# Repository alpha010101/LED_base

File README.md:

チップLEDを筐体に実装するための補助基板

SchematicとPCB_LayoutをAutodesk-Eagle無償版で入力し、elecrowで製造することを前提にガーバーを作成

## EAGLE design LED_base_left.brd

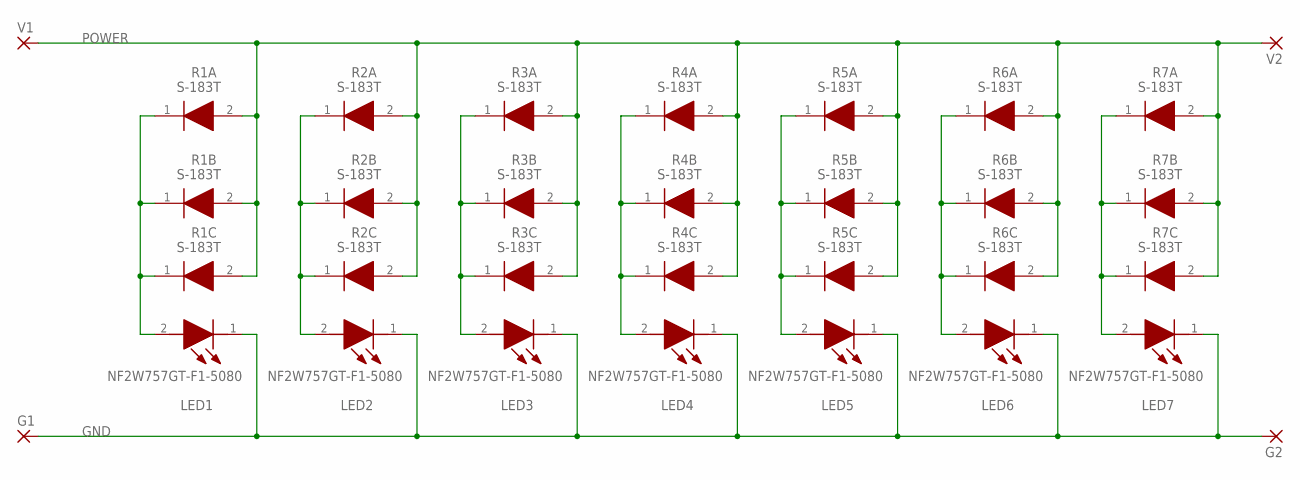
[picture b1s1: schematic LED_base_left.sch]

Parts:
G1: SMD_FULL; SMD3.5-2.5
G2: SMD_HALF; SMD1.75-2.5
LED1, LED2, LED3, LED4, LED5, LED6, LED7: NF2W757GT-F1-5080; NF2W757DRTX
R1A, R1B, R1C, R2A, R2B, R2C, R3A, R3B, R3C, R4A, R4B, R4C, R5A, R5B, R5C, R6A, R6B, R6C, R7A, R7B, R7C: S-183T; SODFL3516X70NX
V1: SMD_FULL; SMD3.5-2.5
V2: SMD_HALF; SMD1.75-2.5

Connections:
GND: G1.1, G2.1, LED1.1 (K), LED2.1 (K), LED3.1 (K), LED4.1 (K), LED5.1 (K), LED6.1 (K), LED7.1 (K)
unnamed: LED1.2 (A), R1A.1 (K), R1B.1 (K), R1C.1 (K)
unnamed: LED2.2 (A), R2A.1 (K), R2B.1 (K), R2C.1 (K)
unnamed: LED3.2 (A), R3A.1 (K), R3B.1 (K), R3C.1 (K)
unnamed: LED4.2 (A), R4A.1 (K), R4B.1 (K), R4C.1 (K)
unnamed: LED5.2 (A), R5A.1 (K), R5B.1 (K), R5C.1 (K)
unnamed: LED6.2 (A), R6A.1 (K), R6B.1 (K), R6C.1 (K)
unnamed: LED7.2 (A), R7A.1 (K), R7B.1 (K), R7C.1 (K)
POWER: R1A.2 (A), R1B.2 (A), R1C.2 (A), R2A.2 (A), R2B.2 (A), R2C.2 (A), R3A.2 (A), R3B.2 (A), R3C.2 (A), R4A.2 (A), R4B.2 (A), R4C.2 (A), R5A.2 (A), R5B.2 (A), R5C.2 (A), R6A.2 (A), R6B.2 (A), R6C.2 (A), R7A.2 (A), R7B.2 (A), R7C.2 (A), V1.1, V2.1

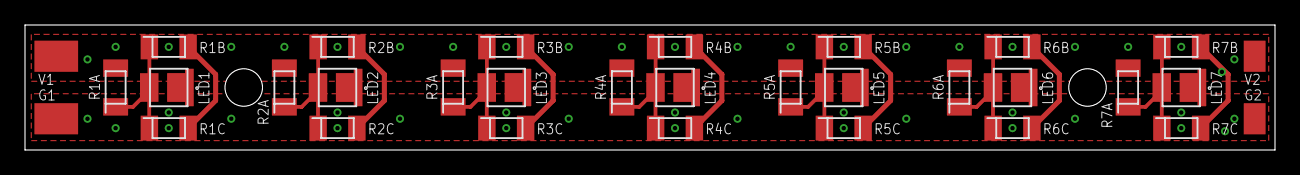
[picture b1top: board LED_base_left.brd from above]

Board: 2 copper layers, 100.0 x 10.0 mm, 32 parts (0 on the bottom side), 9 nets.

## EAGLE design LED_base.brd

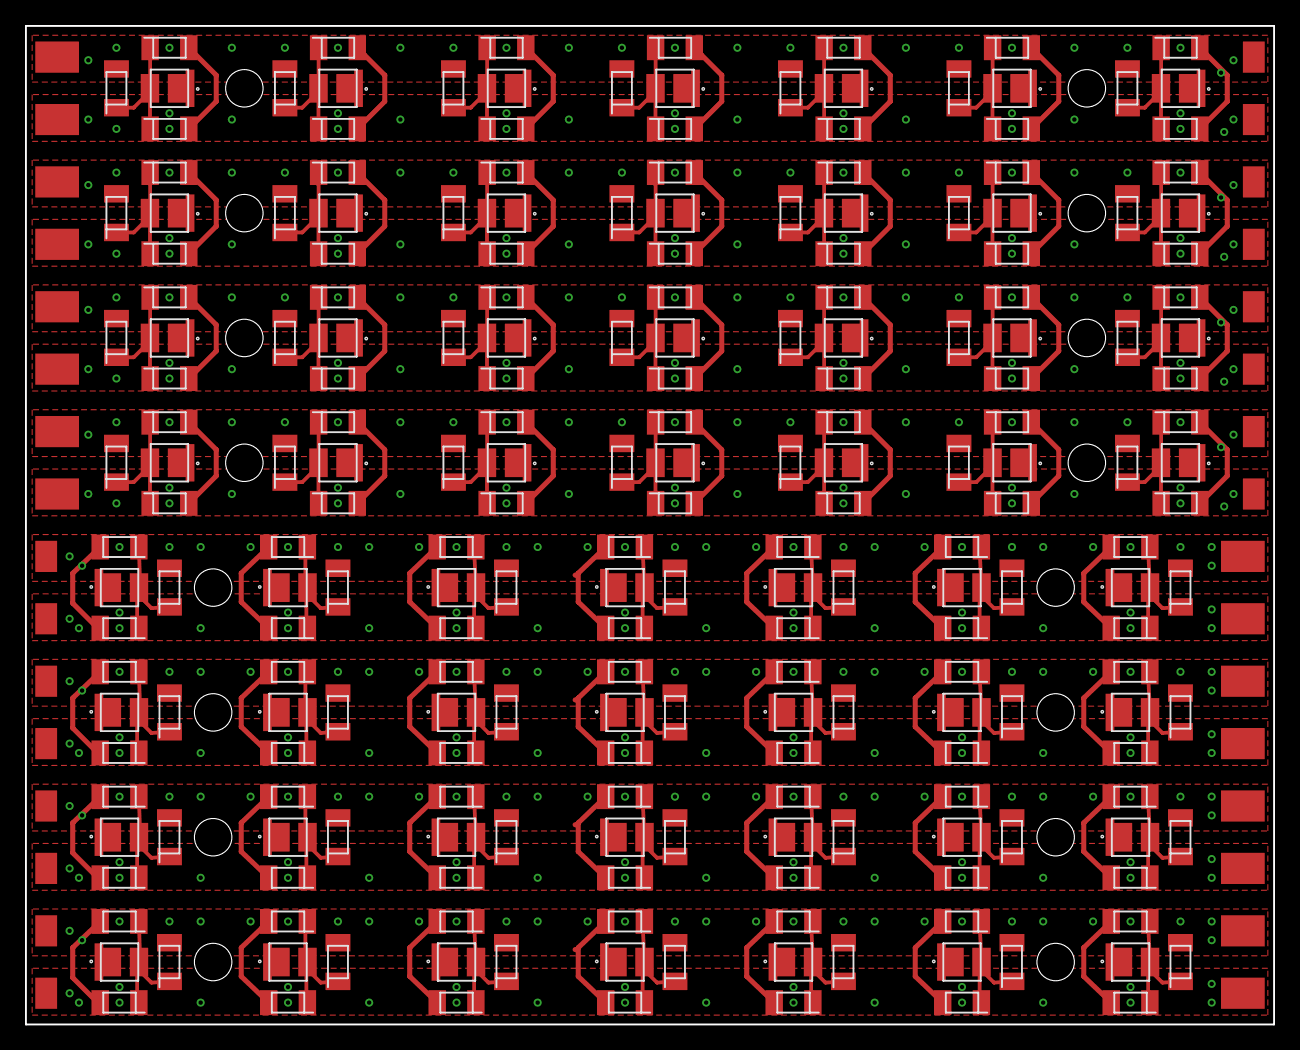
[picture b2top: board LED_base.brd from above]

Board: 2 copper layers, 100.0 x 80.0 mm, 256 parts (0 on the bottom side), 72 nets.

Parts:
G1, G4, G6, G8, G10, G12, G14, G16: SMD1.75-2.5
G2, G3, G5, G7, G9, G11, G13, G15: SMD3.5-2.5
LED1, LED2, LED3, LED4, LED5, LED6, LED7, LED8, LED9, LED10, LED11, LED12, LED13, LED14, LED15, LED16, LED17, LED18, LED19, LED20, LED21, LED22, LED23, LED24, LED25, LED26, LED27, LED28, LED29, LED30, LED31, LED32, LED33, LED34, LED35, LED36, LED37, LED38, LED39, LED40, LED41, LED42, LED43, LED44, LED45, LED46, LED47, LED48, LED49, LED50, LED51, LED52, LED53, LED54, LED55, LED56: NF2W757GT-F1-5080; NF2W757DRTX
R1A, R1A1, R1A2, R1A3, R1B, R1B1, R1B2, R1B3, R1C, R1C1, R1C2, R1C3, R2A, R2A1, R2A2, R2A3, R2B, R2B1, R2B2, R2B3, R2C, R2C1, R2C2, R2C3, R3A, R3A1, R3A2, R3A3, R3B, R3B1, R3B2, R3B3, R3C, R3C1, R3C2, R3C3, R4A, R4A1, R4A2, R4A3, R4B, R4B1, R4B2, R4B3, R4C, R4C1, R4C2, R4C3, R5A, R5A1, R5A2, R5A3, R5B, R5B1, R5B2, R5B3, R5C, R5C1, R5C2, R5C3, R6A, R6A1, R6A2, R6A3, R6B, R6B1, R6B2, R6B3, R6C, R6C1, R6C2, R6C3, R7A, R7A1, R7A2, R7A3, R7B, R7B1, R7B2, R7B3, R7C, R7C1, R7C2, R7C3, R8A, R8A1, R8A2, R8A3, R8B, R8B1, R8B2, R8B3, R8C, R8C1, R8C2, R8C3, R9A, R9A1, R9A2, R9A3, R9B, R9B1, R9B2, R9B3, R9C, R9C1, R9C2, R9C3, R10A, R10A1, R10A2, R10A3, R10B, R10B1, R10B2, R10B3, R10C, R10C1, R10C2, R10C3, R11A, R11A1, R11A2, R11A3, R11B, R11B1, R11B2, R11B3, R11C, R11C1, R11C2, R11C3, R12A, R12A1, R12A2, R12A3, R12B, R12B1, R12B2, R12B3, R12C, R12C1, R12C2, R12C3, R13A, R13A1, R13A2, R13A3, R13B, R13B1, R13B2, R13B3, R13C, R13C1, R13C2, R13C3, R14A, R14A1, R14A2, R14A3, R14B, R14B1, R14B2, R14B3, R14C, R14C1, R14C2, R14C3: S-183T; SODFL3516X70NX
V1, V3, V5, V7, V10, V12, V14, V16: SMD1.75-2.5
V2, V4, V6, V8, V9, V11, V13, V15: SMD3.5-2.5

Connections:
GND: G1.1, G2.1, LED8.1, LED9.1, LED10.1, LED11.1, LED12.1, LED13.1, LED14.1
GND1: G3.1, G4.1, LED1.1, LED2.1, LED3.1, LED4.1, LED5.1, LED6.1, LED7.1
GND2: G5.1, G6.1, LED15.1, LED16.1, LED17.1, LED18.1, LED19.1, LED20.1, LED21.1
GND3: G7.1, G8.1, LED22.1, LED23.1, LED24.1, LED25.1, LED26.1, LED27.1, LED28.1
GND4: G9.1, G10.1, LED29.1, LED30.1, LED31.1, LED32.1, LED33.1, LED34.1, LED35.1
GND5: G11.1, G12.1, LED36.1, LED37.1, LED38.1, LED39.1, LED40.1, LED41.1, LED42.1
GND6: G13.1, G14.1, LED43.1, LED44.1, LED45.1, LED46.1, LED47.1, LED48.1, LED49.1
GND7: G15.1, G16.1, LED50.1, LED51.1, LED52.1, LED53.1, LED54.1, LED55.1, LED56.1
unnamed: LED8.2, R8A.1, R8B.1, R8C.1
unnamed: LED9.2, R9A.1, R9B.1, R9C.1
unnamed: LED10.2, R10A.1, R10B.1, R10C.1
unnamed: LED11.2, R11A.1, R11B.1, R11C.1
unnamed: LED12.2, R12A.1, R12B.1, R12C.1
unnamed: LED13.2, R13A.1, R13B.1, R13C.1
unnamed: LED14.2, R14A.1, R14B.1, R14C.1
unnamed: LED6.2, R8A1.1, R8B1.1, R8C1.1
unnamed: LED7.2, R9A1.1, R9B1.1, R9C1.1
unnamed: LED1.2, R10A1.1, R10B1.1, R10C1.1
unnamed: LED2.2, R11A1.1, R11B1.1, R11C1.1
unnamed: LED3.2, R12A1.1, R12B1.1, R12C1.1
unnamed: LED4.2, R13A1.1, R13B1.1, R13C1.1
unnamed: LED5.2, R14A1.1, R14B1.1, R14C1.1
unnamed: LED20.2, R8A2.1, R8B2.1, R8C2.1
unnamed: LED21.2, R9A2.1, R9B2.1, R9C2.1
unnamed: LED15.2, R10A2.1, R10B2.1, R10C2.1
unnamed: LED16.2, R11A2.1, R11B2.1, R11C2.1
unnamed: LED17.2, R12A2.1, R12B2.1, R12C2.1
unnamed: LED18.2, R13A2.1, R13B2.1, R13C2.1
unnamed: LED19.2, R14A2.1, R14B2.1, R14C2.1
unnamed: LED27.2, R8A3.1, R8B3.1, R8C3.1
unnamed: LED28.2, R9A3.1, R9B3.1, R9C3.1
unnamed: LED22.2, R10A3.1, R10B3.1, R10C3.1
unnamed: LED23.2, R11A3.1, R11B3.1, R11C3.1
unnamed: LED24.2, R12A3.1, R12B3.1, R12C3.1
unnamed: LED25.2, R13A3.1, R13B3.1, R13C3.1
unnamed: LED26.2, R14A3.1, R14B3.1, R14C3.1
unnamed: LED29.2, R1A.1, R1B.1, R1C.1
unnamed: LED30.2, R2A.1, R2B.1, R2C.1
unnamed: LED31.2, R3A.1, R3B.1, R3C.1
unnamed: LED32.2, R4A.1, R4B.1, R4C.1
unnamed: LED33.2, R5A.1, R5B.1, R5C.1
unnamed: LED34.2, R6A.1, R6B.1, R6C.1
unnamed: LED35.2, R7A.1, R7B.1, R7C.1
unnamed: LED36.2, R1A1.1, R1B1.1, R1C1.1
unnamed: LED37.2, R2A1.1, R2B1.1, R2C1.1
unnamed: LED38.2, R3A1.1, R3B1.1, R3C1.1
unnamed: LED39.2, R4A1.1, R4B1.1, R4C1.1
unnamed: LED40.2, R5A1.1, R5B1.1, R5C1.1
unnamed: LED41.2, R6A1.1, R6B1.1, R6C1.1
unnamed: LED42.2, R7A1.1, R7B1.1, R7C1.1
unnamed: LED43.2, R1A2.1, R1B2.1, R1C2.1
unnamed: LED44.2, R2A2.1, R2B2.1, R2C2.1
unnamed: LED45.2, R3A2.1, R3B2.1, R3C2.1
unnamed: LED46.2, R4A2.1, R4B2.1, R4C2.1
unnamed: LED47.2, R5A2.1, R5B2.1, R5C2.1
unnamed: LED48.2, R6A2.1, R6B2.1, R6C2.1
unnamed: LED49.2, R7A2.1, R7B2.1, R7C2.1
unnamed: LED50.2, R1A3.1, R1B3.1, R1C3.1
unnamed: LED51.2, R2A3.1, R2B3.1, R2C3.1
unnamed: LED52.2, R3A3.1, R3B3.1, R3C3.1
unnamed: LED53.2, R4A3.1, R4B3.1, R4C3.1
unnamed: LED54.2, R5A3.1, R5B3.1, R5C3.1
unnamed: LED55.2, R6A3.1, R6B3.1, R6C3.1
unnamed: LED56.2, R7A3.1, R7B3.1, R7C3.1
POWER: R8A.2, R8B.2, R8C.2, R9A.2, R9B.2, R9C.2, R10A.2, R10B.2, R10C.2, R11A.2, R11B.2, R11C.2, R12A.2, R12B.2, R12C.2, R13A.2, R13B.2, R13C.2, R14A.2, R14B.2, R14C.2, V1.1, V2.1
POWER1: R8A1.2, R8B1.2, R8C1.2, R9A1.2, R9B1.2, R9C1.2, R10A1.2, R10B1.2, R10C1.2, R11A1.2, R11B1.2, R11C1.2, R12A1.2, R12B1.2, R12C1.2, R13A1.2, R13B1.2, R13C1.2, R14A1.2, R14B1.2, R14C1.2, V3.1, V4.1
POWER2: R8A2.2, R8B2.2, R8C2.2, R9A2.2, R9B2.2, R9C2.2, R10A2.2, R10B2.2, R10C2.2, R11A2.2, R11B2.2, R11C2.2, R12A2.2, R12B2.2, R12C2.2, R13A2.2, R13B2.2, R13C2.2, R14A2.2, R14B2.2, R14C2.2, V5.1, V6.1
POWER3: R8A3.2, R8B3.2, R8C3.2, R9A3.2, R9B3.2, R9C3.2, R10A3.2, R10B3.2, R10C3.2, R11A3.2, R11B3.2, R11C3.2, R12A3.2, R12B3.2, R12C3.2, R13A3.2, R13B3.2, R13C3.2, R14A3.2, R14B3.2, R14C3.2, V7.1, V8.1
POWER4: R1A.2, R1B.2, R1C.2, R2A.2, R2B.2, R2C.2, R3A.2, R3B.2, R3C.2, R4A.2, R4B.2, R4C.2, R5A.2, R5B.2, R5C.2, R6A.2, R6B.2, R6C.2, R7A.2, R7B.2, R7C.2, V9.1, V10.1
POWER5: R1A1.2, R1B1.2, R1C1.2, R2A1.2, R2B1.2, R2C1.2, R3A1.2, R3B1.2, R3C1.2, R4A1.2, R4B1.2, R4C1.2, R5A1.2, R5B1.2, R5C1.2, R6A1.2, R6B1.2, R6C1.2, R7A1.2, R7B1.2, R7C1.2, V11.1, V12.1
POWER6: R1A2.2, R1B2.2, R1C2.2, R2A2.2, R2B2.2, R2C2.2, R3A2.2, R3B2.2, R3C2.2, R4A2.2, R4B2.2, R4C2.2, R5A2.2, R5B2.2, R5C2.2, R6A2.2, R6B2.2, R6C2.2, R7A2.2, R7B2.2, R7C2.2, V13.1, V14.1
POWER7: R1A3.2, R1B3.2, R1C3.2, R2A3.2, R2B3.2, R2C3.2, R3A3.2, R3B3.2, R3C3.2, R4A3.2, R4B3.2, R4C3.2, R5A3.2, R5B3.2, R5C3.2, R6A3.2, R6B3.2, R6C3.2, R7A3.2, R7B3.2, R7C3.2, V15.1, V16.1

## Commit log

2025-01-02 initial release

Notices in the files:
LED_base.brd:
(C)2021 BRIGHT-CHIPS
